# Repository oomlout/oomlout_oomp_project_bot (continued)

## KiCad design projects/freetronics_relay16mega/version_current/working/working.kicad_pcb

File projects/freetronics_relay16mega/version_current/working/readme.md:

# RELAY16MEGA by freetronics  
This is a harvested standardized copy of a project from github.  
The original project can be found at:  
https://github.com/freetronics/RELAY16MEGA  
Please consult that link for additional, details, files, and license information.  
Note: It was auto harvested and if the original repo had more than one board file or anything out of the ordinary the files here are likely not representative.

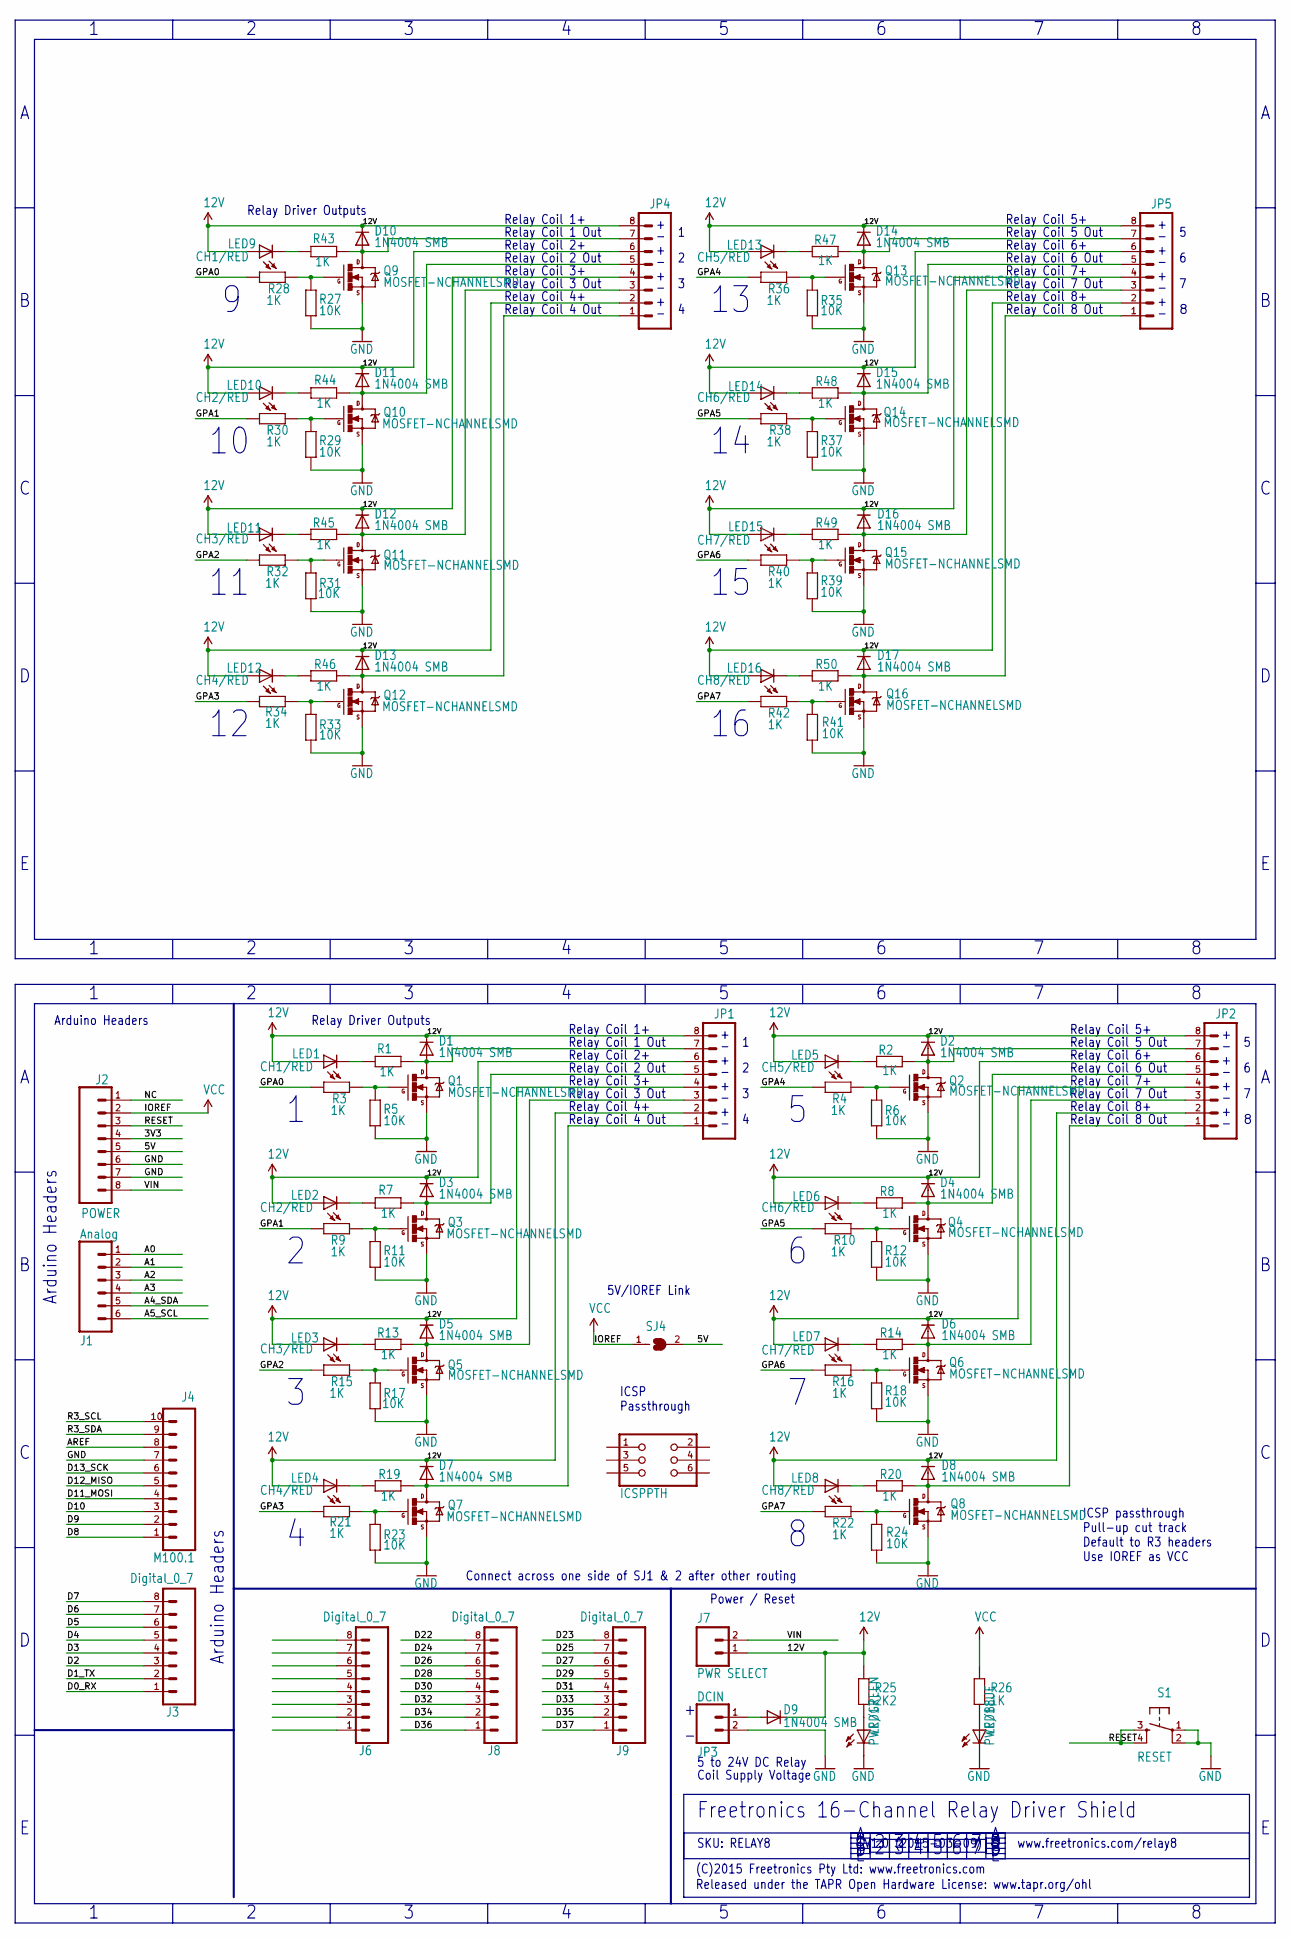
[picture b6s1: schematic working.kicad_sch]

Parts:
D1, D2, D3, D4, D5, D6, D7, D8, D9, D10, D11, D12, D13, D14, D15, D16, D17: 1N4004 SMB; SMB-DIODE
J1: Analog; 1X06
J2: POWER; 1X08
J3, J6, J8, J9: Digital_0_7; 1X08
J4: M100.1; 1X10
J5: ICSPPTH; 2X03PTH
J7: PWR SELECT; 1X02
JP1, JP2, JP4, JP5: M08; TERMINALBLOCK_3.5MM_8
JP3: DCIN; SCREWTERMINAL-3.5MM-2
LED1, LED9: CH1/RED; LED-0603
LED2, LED10: CH2/RED; LED-0603
LED3, LED11: CH3/RED; LED-0603
LED4, LED12: CH4/RED; LED-0603
LED5, LED13: CH5/RED; LED-0603
LED6, LED14: CH6/RED; LED-0603
LED7, LED15: CH7/RED; LED-0603
LED8, LED16: CH8/RED; LED-0603
LED17: PWR/GREEN; LED-0603
LED18: PWR/BLUE; LED-0603
Q1, Q2, Q3, Q4, Q5, Q6, Q7, Q8, Q9, Q10, Q11, Q12, Q13, Q14, Q15, Q16: MOSFET-NCHANNELSMD; SOT23-3
R1, R2, R3, R4, R7, R8, R9, R10, R13, R14, R15, R16, R19, R20, R21, R22, R26, R28, R30, R32, R34, R36, R38, R40, R42, R43, R44, R45, R46, R47, R48, R49, R50: 1K; 0603
R5, R6, R11, R12, R17, R18, R23, R24, R27, R29, R31, R33, R35, R37, R39, R41: 10K; 0603
R25: 2K2; 0603
S1: RESET; TACTILE_SWITCH_SMD
SJ4: SJN; SJ

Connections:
3V3: J2.4
5V: J2.5, SJ4.2
12V: D1.C, D2.C, D3.C, D4.C, D5.C, D6.C, D7.C, D8.C, D9.C, D10.C, D11.C, D12.C, D13.C, D14.C, D15.C, D16.C, D17.C, J7.1, JP1.2, JP1.4, JP1.6, JP1.8, JP2.2, JP2.4, JP2.6, JP2.8, JP4.2, JP4.4, JP4.6, JP4.8, JP5.2, JP5.4, JP5.6, JP5.8, LED1.A, LED2.A, LED3.A, LED4.A, LED5.A, LED6.A, LED7.A, LED8.A, LED9.A, LED10.A, LED11.A, LED12.A, LED13.A, LED14.A, LED15.A, LED16.A, R25.2
A0: J1.1
A1: J1.2
A2: J1.3
A3: J1.4
A4_SDA: J1.5
A5_SCL: J1.6
AREF: J4.8
D0_RX: J3.1
D1_TX: J3.2
D2: J3.3
D3: J3.4
D4: J3.5
D5: J3.6
D6: J3.7
D7: J3.8
D8: J4.1
D9: J4.2
D10: J4.3
D11_MOSI: J4.4
D12_MISO: J4.5
D13_SCK: J4.6
D22: J8.8
D23: J9.8
D24: J8.7
D25: J9.7
D26: J8.6
D27: J9.6
D28: J8.5
D29: J9.5
D30: J8.4
D31: J9.4
D32: J8.3
D33: J9.3
D34: J8.2
D35: J9.2
D36: J8.1
D37: J9.1
GND: J2.6, J2.7, J4.7, JP3.2, LED17.C, LED18.C, Q1.2 (S), Q2.2 (S), Q3.2 (S), Q4.2 (S), Q5.2 (S), Q6.2 (S), Q7.2 (S), Q8.2 (S), Q9.2 (S), Q10.2 (S), Q11.2 (S), Q12.2 (S), Q13.2 (S), Q14.2 (S), Q15.2 (S), Q16.2 (S), R5.1, R6.1, R11.1, R12.1, R17.1, R18.1, R23.1, R24.1, R27.1, R29.1, R31.1, R33.1, R35.1, R37.1, R39.1, R41.1, S1.1, S1.2
GPA0: R3.2, R28.2
GPA1: R9.2, R30.2
GPA2: R15.2, R32.2
GPA3: R21.2, R34.2
GPA4: R4.2, R36.2
GPA5: R10.2, R38.2
GPA6: R16.2, R40.2
GPA7: R22.2, R42.2
IOREF: J2.2, R26.2, SJ4.1
unnamed: Q1.1 (G), R3.1, R5.2
unnamed: D3.A, JP1.5, Q3.3 (D), R7.2
unnamed: LED17.A, R25.1
unnamed: D1.A, JP1.7, Q1.3 (D), R1.2
unnamed: Q3.1 (G), R9.1, R11.2
unnamed: D5.A, JP1.3, Q5.3 (D), R13.2
unnamed: Q5.1 (G), R15.1, R17.2
unnamed: D7.A, JP1.1, Q7.3 (D), R19.2
unnamed: Q7.1 (G), R21.1, R23.2
unnamed: D2.A, JP2.7, Q2.3 (D), R2.2
unnamed: Q2.1 (G), R4.1, R6.2
unnamed: D4.A, JP2.5, Q4.3 (D), R8.2
unnamed: Q4.1 (G), R10.1, R12.2
unnamed: D6.A, JP2.3, Q6.3 (D), R14.2
unnamed: Q6.1 (G), R16.1, R18.2
unnamed: D8.A, JP2.1, Q8.3 (D), R20.2
unnamed: Q8.1 (G), R22.1, R24.2
unnamed: LED2.C, R7.1
unnamed: LED4.C, R19.1
unnamed: LED3.C, R13.1
unnamed: LED1.C, R1.1
unnamed: LED5.C, R2.1
unnamed: LED6.C, R8.1
unnamed: LED7.C, R14.1
unnamed: LED8.C, R20.1
unnamed: D9.A, JP3.1
unnamed: D10.A, JP4.7, Q9.3 (D), R43.2
unnamed: Q9.1 (G), R27.2, R28.1
unnamed: D11.A, JP4.5, Q10.3 (D), R44.2
unnamed: Q10.1 (G), R29.2, R30.1
unnamed: D12.A, JP4.3, Q11.3 (D), R45.2
unnamed: Q11.1 (G), R31.2, R32.1
unnamed: LED18.A, R26.1
unnamed: D13.A, JP4.1, Q12.3 (D), R46.2
unnamed: Q12.1 (G), R33.2, R34.1
unnamed: D14.A, JP5.7, Q13.3 (D), R47.2
unnamed: Q13.1 (G), R35.2, R36.1
unnamed: D15.A, JP5.5, Q14.3 (D), R48.2
unnamed: Q14.1 (G), R37.2, R38.1
unnamed: D16.A, JP5.3, Q15.3 (D), R49.2
unnamed: Q15.1 (G), R39.2, R40.1
unnamed: D17.A, JP5.1, Q16.3 (D), R50.2
unnamed: Q16.1 (G), R41.2, R42.1
unnamed: LED9.C, R43.1
unnamed: LED10.C, R44.1
unnamed: LED11.C, R45.1
unnamed: LED12.C, R46.1
unnamed: LED13.C, R47.1
unnamed: LED14.C, R48.1
unnamed: LED15.C, R49.1
unnamed: LED16.C, R50.1
NC: J2.1
R3_SCL: J4.10
R3_SDA: J4.9
RESET: J2.3, S1.3, S1.4
VIN: J2.8, J7.2

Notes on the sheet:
Relay Coil 2 Out
ICSP Passthrough
Relay Coil 7+
Freetronics 16-Channel Relay Driver Shield
Relay Coil 4+
5V/IOREF Link
Relay Coil 4 Out
Relay Coil 3 Out
5 to 24V DC Relay
Relay Coil 6+
Relay Coil 1 Out
Relay Coil 5+
Relay Driver Outputs
SKU: RELAY8
Relay Coil 6 Out
V1.0 (2015-03-09)
(C)2015 Freetronics Pty Ltd: www.freetronics.com
Arduino Headers
Relay Coil 3+
Relay Coil 8 Out
Coil Supply Voltage
Relay Coil 7 Out
Connect across one side of SJ1 & 2 after other routing
Relay Coil 2+
Relay Coil 1+
Relay Coil 8+
Power / Reset
Relay Coil 5 Out
www.freetronics.com/relay8
Released under the TAPR Open Hardware License: www.tapr.org/ohl
ICSP passthrough Pull-up cut track Default to R3 headers Use IOREF as VCC

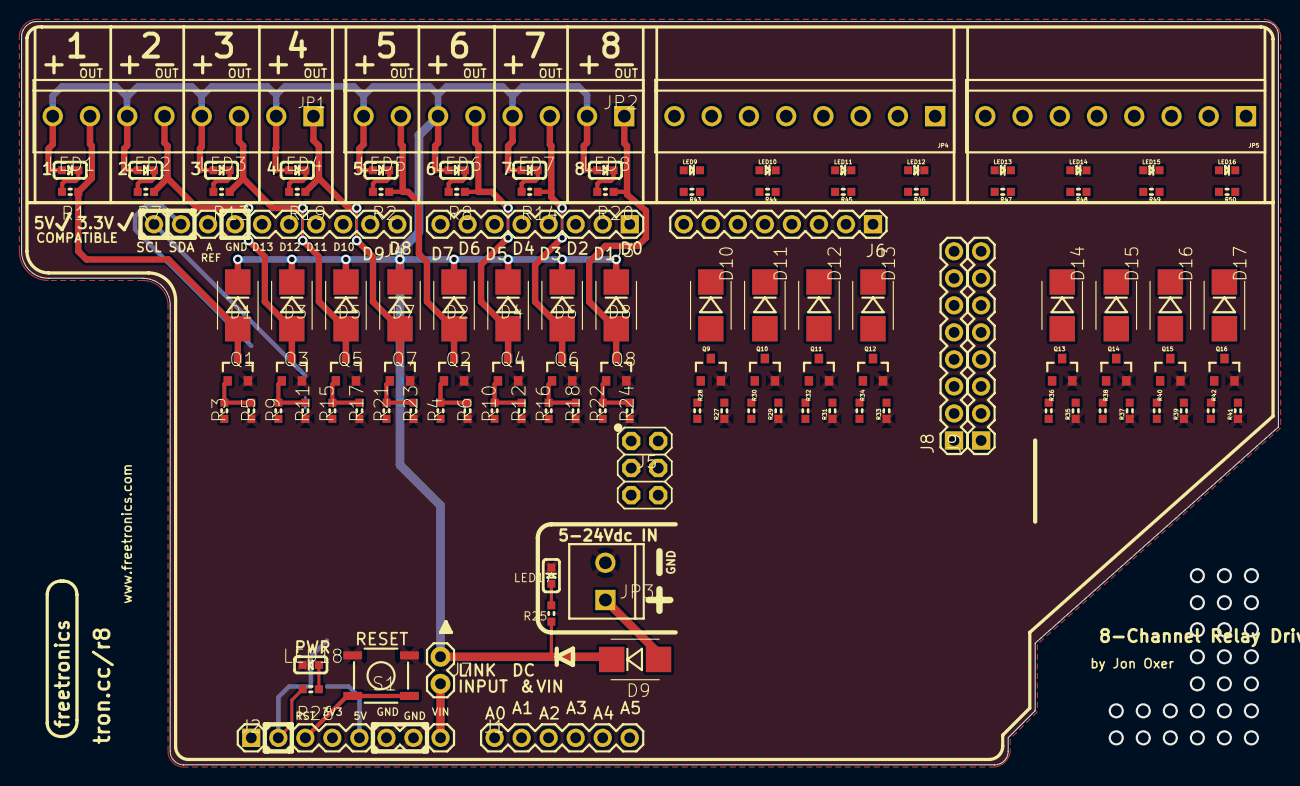
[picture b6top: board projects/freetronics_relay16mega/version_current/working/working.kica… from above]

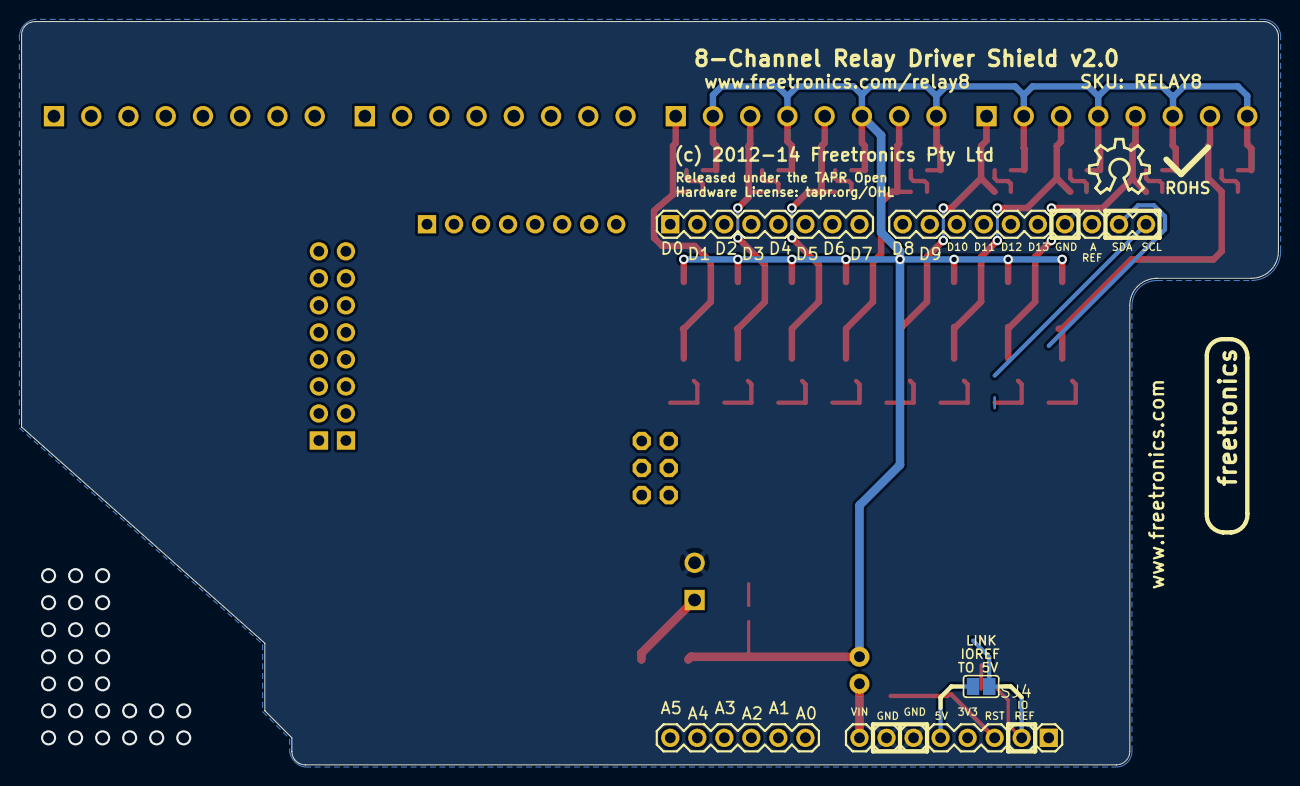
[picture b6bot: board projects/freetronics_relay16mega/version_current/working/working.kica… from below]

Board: 2 copper layers, 118.1 x 69.8 mm, 118 parts (2 on the bottom side), 65 nets.

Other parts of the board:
U$6: OSHW_10X200_NOTEXT

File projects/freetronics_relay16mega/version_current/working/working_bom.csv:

"Id";"Designator";"Footprint";"Quantity";"Designation";"Supplier and ref";
1;"LED4,LED12";"LED-0603";2;"CH4/RED";;;
2;"J2";"1X08";1;"POWER";;;
3;"R41,R24,R18,R33,R37,R5,R35,R39,R29,R6,R11,R23,R27,R31,R17,R12";"0603";16;"10K";;;
4;"R1,R45,R50,R46,R20,R13,R32,R44,R21,R10,R2,R22,R4,R40,R15,R34,R30,R19,R38,R42,R49,R28,R36,R3,R16,R26,R9,R7,R43,R8,R48,R14,R47";"0603";33;"1K";;;
5;"Q12,Q11,Q10,Q3,Q7,Q14,Q1,Q16,Q15,Q8,Q5,Q9,Q13,Q2,Q4,Q6";"SOT23-3";16;"2N7002";;;
6;"D10,D1,D16,D3,D6,D14,D12,D15,D5,D4,D13,D17,D9,D2,D11,D7,D8";"SMB-DIODE";17;"1N4004 SMB";;;
7;"JP1,JP2,JP4,JP5";"TERMINALBLOCK_3.5MM_8";4;"";;;
8;"LED1,LED9";"LED-0603";2;"CH1/RED";;;
9;"S1";"TACTILE_SWITCH_SMD";1;"RESET";;;
10;"J8,J3,J6,J9";"1X08";4;"Digital_0_7";;;
11;"J1";"1X06";1;"Analog";;;
12;"LED13,LED5";"LED-0603";2;"CH5/RED";;;
13;"LED6,LED14";"LED-0603";2;"CH6/RED";;;
14;"LED15,LED7";"LED-0603";2;"CH7/RED";;;
15;"R25";"0603";1;"2K2";;;
16;"LED8,LED16";"LED-0603";2;"CH8/RED";;;
17;"J5";"2X03PTH";1;"ICSPPTH";;;
18;"LED10,LED2";"LED-0603";2;"CH2/RED";;;
19;"LED3,LED11";"LED-0603";2;"CH3/RED";;;
20;"JP3";"SCREWTERMINAL-3.5MM-2";1;"DCIN";;;
21;"J7";"1X02";1;"PWR SELECT";;;
22;"J4";"1X10";1;"M100.1";;;
23;"LED18";"LED-0603";1;"PWR/BLUE";;;
24;"LED17";"LED-0603";1;"PWR/GREEN";;;
25;"U$6";"OSHW_10X200_NOTEXT";1;"";;;
26;"SJ4";"SJ";1;"";;;
